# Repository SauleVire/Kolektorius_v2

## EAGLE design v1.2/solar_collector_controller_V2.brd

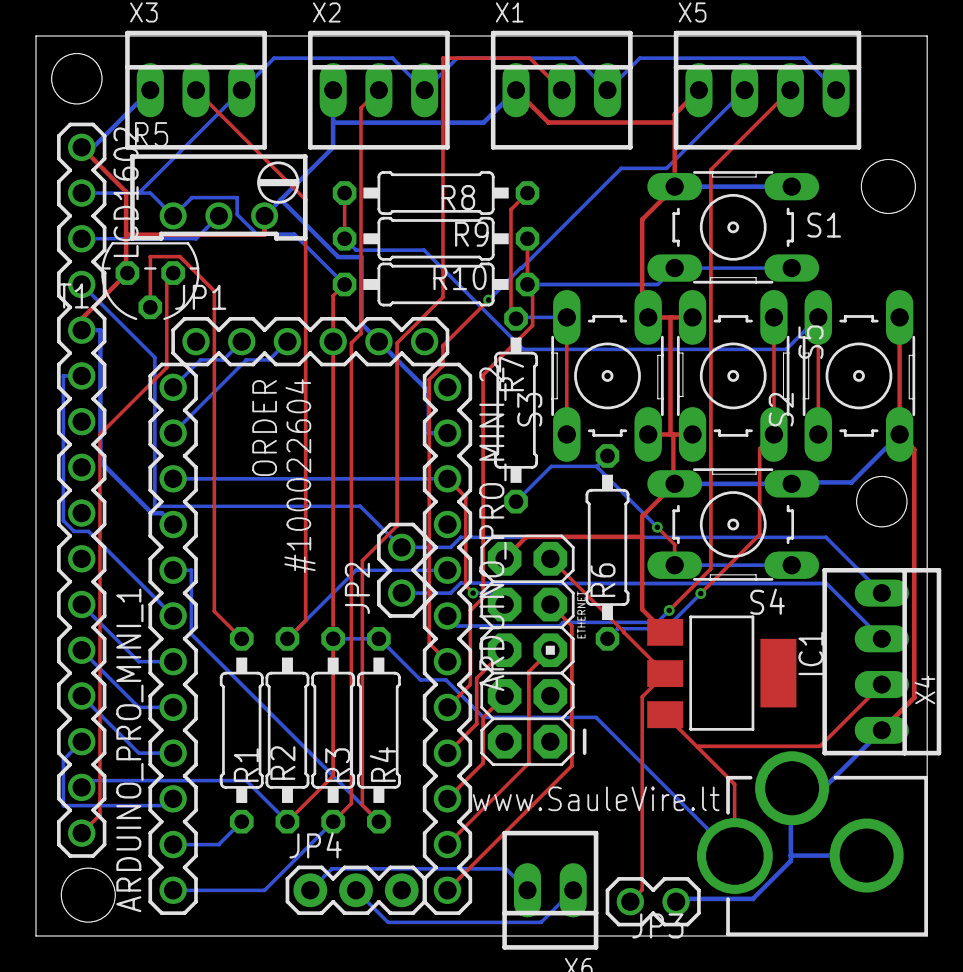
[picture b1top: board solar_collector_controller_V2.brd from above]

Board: 2 copper layers, 49.5 x 50.0 mm, 32 parts (0 on the bottom side), 33 nets.

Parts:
ARDUINO_PRO_MINI_1, ARDUINO_PRO_MINI_2: 1X12
ETHERNET: ENC25J60; AVR_ICSP
IC1: REG1117; SOT223
J1: POWER; POWER_JACK_PTH_LOCK
JP1: DTR TX RX VCC GDN; 1X06
JP2: 1X02
JP3: GND 3.3V; 1X02
JP4: 1X03
LCD1602: 16P-2.54
R1: 2k2; 0207/10
R2, R3, R4: 4k7; 0207/10
R5: 10k; RTRIM64W
R6: 3k3; 0207/10
R7: 1k; 0207/10
R8: 620; 0207/10
R9: 330; 0207/10
R10: 2k; 0207/10
S1: Right; B3F-10XX
S2: Up; B3F-10XX
S3: Down; B3F-10XX
S4: Left; B3F-10XX
S5: Select; B3F-10XX
T1: BC337; TO92
X1: VCC D2 GND; 22-23-2031
X2: VCC D9 GND; 22-23-2031
X3: VCC A3 GND; 22-23-2031
X4: GND A5 A4 VCC; 22-23-2041
X5: VCC A2 A1 GND; 22-23-2041
X6: A6 A7; 22-23-2021

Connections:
3.3V: ETHERNET.9, IC1.2, JP3.1
A0: ARDUINO_PRO_MINI_2.8, R9.2, R10.1, S1.1, S1.2
A1: ARDUINO_PRO_MINI_2.7, X5.2
A2: ARDUINO_PRO_MINI_2.6, X5.3
A3: ARDUINO_PRO_MINI_2.5, R2.2, X3.2
A4: JP2.1, X4.2
A5: JP2.2, LCD1602.4, X4.1
A6: JP4.2, X6.1
A7: JP4.1, X6.2
D2: ARDUINO_PRO_MINI_1.8, R4.2, X1.2
D3: ARDUINO_PRO_MINI_1.7, LCD1602.6
D4: ARDUINO_PRO_MINI_1.6, LCD1602.11
D5: ARDUINO_PRO_MINI_1.5, LCD1602.12
D6: ARDUINO_PRO_MINI_1.4, LCD1602.13
D7: ARDUINO_PRO_MINI_1.3, LCD1602.14
D8: ARDUINO_PRO_MINI_1.2, R1.2
D9: ARDUINO_PRO_MINI_1.1, R3.2, X2.2
D10: ARDUINO_PRO_MINI_2.12, ETHERNET.7
D11: ARDUINO_PRO_MINI_2.11, ETHERNET.5
D12: ARDUINO_PRO_MINI_2.10, ETHERNET.4
D13: ARDUINO_PRO_MINI_2.9, ETHERNET.6
GND: ARDUINO_PRO_MINI_1.9, ARDUINO_PRO_MINI_2.2, ETHERNET.10, IC1.1, J1.GND, J1.GNDBREAK, JP1.5, JP3.2, LCD1602.1, LCD1602.5, R5.3, S1.3, S1.4, S2.3, S2.4, S3.3, S3.4, S4.3, S4.4, S5.3, S5.4, T1.1, X1.1, X2.1, X3.1, X4.4, X5.1
LCD16: LCD1602.16, T1.3
unnamed: LCD1602.3, R5.2
unnamed: R1.1, T1.2
unnamed: R6.1, S5.1, S5.2
unnamed: R6.2, R7.1, S4.1, S4.2
unnamed: R7.2, R8.1, S3.1, S3.2
unnamed: R8.2, R9.1, S2.1, S2.2
RESET: ARDUINO_PRO_MINI_1.10, ARDUINO_PRO_MINI_2.3, ETHERNET.8
RXI: ARDUINO_PRO_MINI_1.11, JP1.3
TXO: ARDUINO_PRO_MINI_1.12, JP1.2
VCC: IC1.3, J1.PWR, JP1.4, LCD1602.2, LCD1602.15, R2.1, R3.1, R4.1, R5.1, R10.2, X1.3, X2.3, X3.3, X4.3, X5.4

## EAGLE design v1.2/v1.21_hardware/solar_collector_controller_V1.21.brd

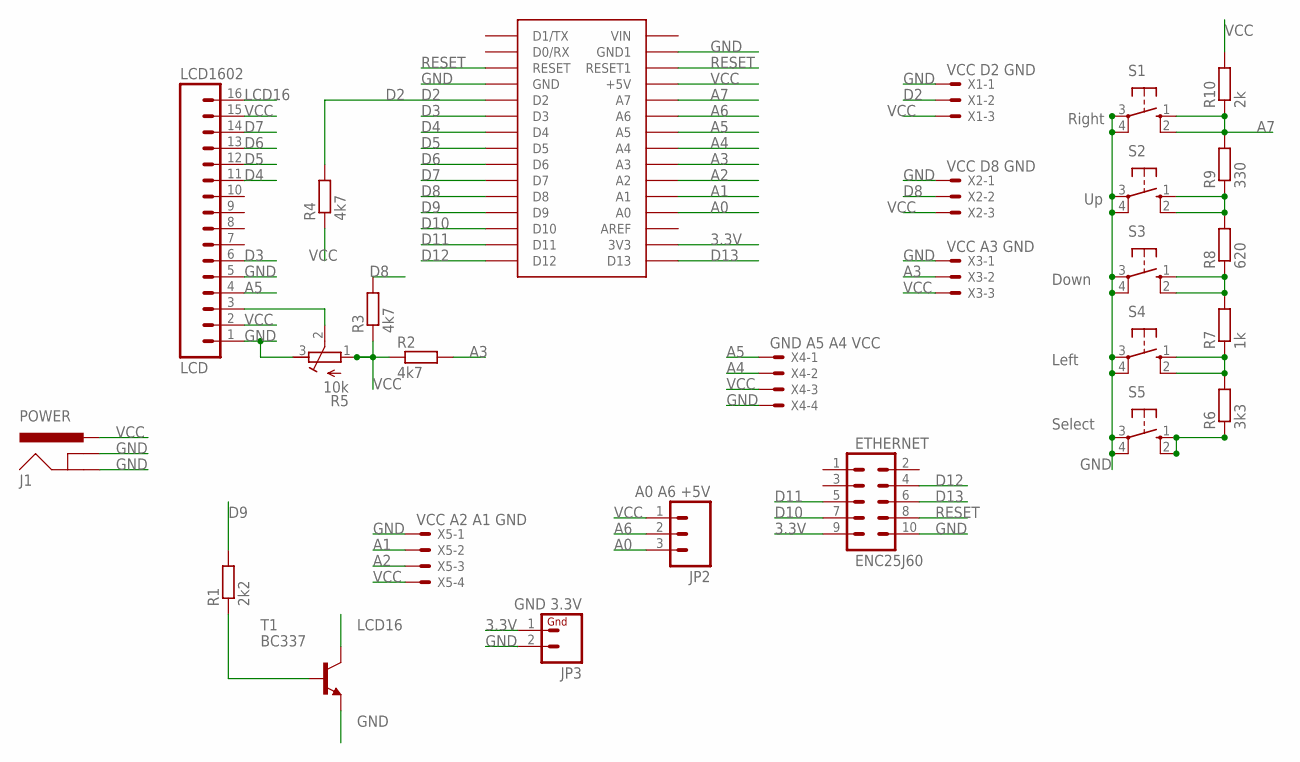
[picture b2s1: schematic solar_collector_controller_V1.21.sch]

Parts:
ETHERNET: ENC25J60; AVR_ICSP
J1: POWER; POWER_JACK_PTH_LOCK
JP2: A0 A6 +5V; 1X03
JP3: GND 3.3V; 1X02
LCD1602: LCD; 16P-2.54
R1: 2k2; 0207/10
R2, R3, R4: 4k7; 0207/10
R5: 10k; RTRIM64W
R6: 3k3; 0207/10
R7: 1k; 0207/10
R8: 620; 0207/10
R9: 330; 0207/10
R10: 2k; 0207/10
S1: Right; B3F-10XX
S2: Up; B3F-10XX
S3: Down; B3F-10XX
S4: Left; B3F-10XX
S5: Select; B3F-10XX
T1: BC337; TO92
U$2: ARDUINONANO; PDIP-32
X1: VCC D2 GND; 22-23-2031
X2: VCC D8 GND; 22-23-2031
X3: VCC A3 GND; 22-23-2031
X4: GND A5 A4 VCC; 22-23-2041
X5: VCC A2 A1 GND; 22-23-2041

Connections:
3.3V: ETHERNET.9, JP3.1, U$2.3V3
A0: JP2.3, U$2.A0
A1: U$2.A1, X5.2
A2: U$2.A2, X5.3
A3: R2.2, U$2.A3, X3.2
A4: U$2.A4, X4.2
A5: LCD1602.4, U$2.A5, X4.1
A6: JP2.2, U$2.A6
A7: R9.2, R10.1, S1.1 (S), S1.2 (S1), U$2.A7
D2: R4.2, U$2.D2, X1.2
D3: LCD1602.6, U$2.D3
D4: LCD1602.11, U$2.D4
D5: LCD1602.12, U$2.D5
D6: LCD1602.13, U$2.D6
D7: LCD1602.14, U$2.D7
D8: R3.2, U$2.D8, X2.2
D9: R1.2, U$2.D9
D10: ETHERNET.7, U$2.D10
D11: ETHERNET.5, U$2.D11
D12: ETHERNET.4, U$2.D12
D13: ETHERNET.6, U$2.D13
GND: ETHERNET.10, J1.GND, J1.GNDBREAK, JP3.2, LCD1602.1, LCD1602.5, R5.3 (A), S1.3, S1.4 (P1), S2.3, S2.4 (P1), S3.3, S3.4 (P1), S4.3, S4.4 (P1), S5.3, S5.4 (P1), T1.1 (E), U$2.GND, U$2.GND1, X1.1, X2.1, X3.1, X4.4, X5.1
LCD16: LCD1602.16, T1.3 (C)
unnamed: LCD1602.3, R5.2 (S)
unnamed: R1.1, T1.2 (B)
unnamed: R6.1, S5.1 (S), S5.2 (S1)
unnamed: R6.2, R7.1, S4.1 (S), S4.2 (S1)
unnamed: R7.2, R8.1, S3.1 (S), S3.2 (S1)
unnamed: R8.2, R9.1, S2.1 (S), S2.2 (S1)
RESET: ETHERNET.8, U$2.RESET, U$2.RESET1
VCC: J1.PWR, JP2.1, LCD1602.2, LCD1602.15, R2.1, R3.1, R4.1, R5.1 (E), R10.2, U$2.+5V, X1.3, X2.3, X3.3, X4.3, X5.4

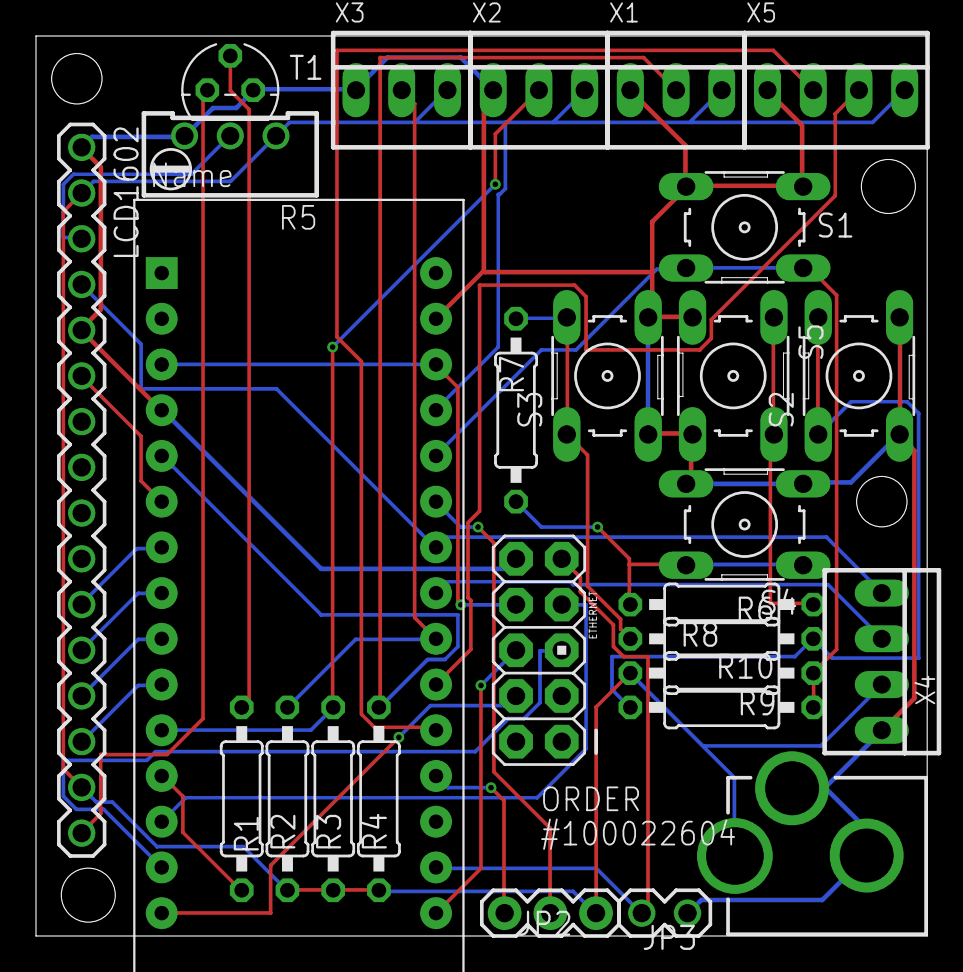
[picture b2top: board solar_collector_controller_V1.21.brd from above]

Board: 2 copper layers, 49.5 x 50.0 mm, 27 parts (0 on the bottom side), 31 nets.

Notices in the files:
parts and their libraries:
SparkFun-Connectors: Licensing: CC v3.0 Share-Alike You are welcome to use this library for commercial purposes.
